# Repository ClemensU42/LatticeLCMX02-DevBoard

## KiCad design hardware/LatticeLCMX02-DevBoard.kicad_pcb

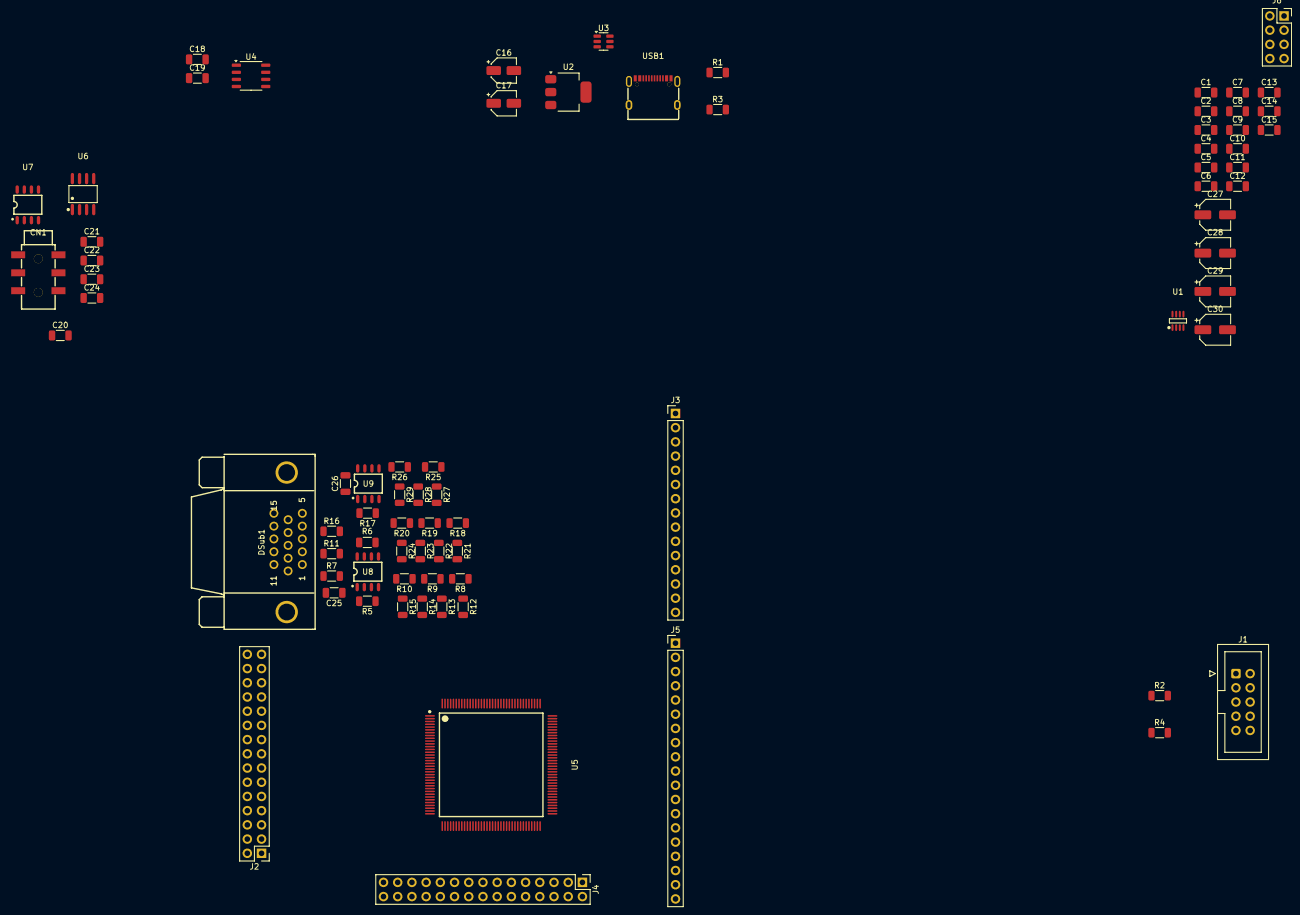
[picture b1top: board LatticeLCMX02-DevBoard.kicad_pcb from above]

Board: 4 copper layers, 77 parts (0 on the bottom side), 143 nets, no tracks yet.

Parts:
C1, C2, C3, C4, C5, C6, C7, C8, C9, C10, C11, C12, C13, C14, C15, C24, C25, C26: 470nF; C_1206_3216Metric
C16: 10µF; CP_Elec_4x5.4
C17: 22µF; CP_Elec_4x5.4
C18, C19: 0.1µF; C_1206_3216Metric
C20: 47µF; C_1206_3216Metric
C21, C22, C23: 100nF; C_1206_3216Metric
C27, C28, C29, C30: 47µF; CP_Elec_5x5.4
CN1: PJ-313D_C668608; AUDIO-SMD_PJ-313D-2
DSub1: DS1038-15FBNSIA74-0CC; DSUB-TH_DS1038-15FBNSIA74-0CC
J1: Conn_02x05_Odd_Even; IDC-Header_2x05_P2.54mm_Vertical
J2, J4: Conn_02x15_Counter_Clockwise; PinHeader_2x15_P2.54mm_Vertical
J3: Conn_01x15; PinHeader_1x15_P2.54mm_Vertical
J5: Conn_01x19; PinHeader_1x19_P2.54mm_Vertical
J6: Conn_02x04_Counter_Clockwise; PinSocket_2x04_P2.54mm_Vertical
R1, R3: 5k1; R_1206_3216Metric
R2, R4: 4k7; R_1206_3216Metric
R5, R6, R17: 220; R_1206_3216Metric
R7, R11, R16: 75; R_1206_3216Metric
R8, R9, R10, R18, R19, R20, R25, R26: 1k; R_1206_3216Metric
R12, R13, R14, R15, R21, R22, R23, R24, R27, R28, R29: 2k; R_1206_3216Metric
U1: RS0102YH8; SOT-23-8_L3.0-W1.7-P0.65-LS2.8-BL
U2: AMS1117-3.3; SOT-223-3_TabPin2
U3: USBLC6-2SC6; SOT-23-6
U4: CH340N; SOP-8_3.9x4.9mm_P1.27mm
U5: LCMXO2-4000HC-4TG144C; TQFP-144_L20.0-W20.0-P0.50-LS22.0-BL
U6: TM8211-TA2302; SOIC-8_L4.9-W3.9-P1.27-LS6.0-BL
U7, U8, U9: HG5532M/TR; SOP-8_L5.0-W3.9-P1.27-LS6.0-BL
USB1: TYPE-C 16PIN 2MD(073); USB-C-SMD_TYPE-C-6PIN-2MD-073

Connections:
+3.3V: C1.1, C2.1, C3.1, C4.1, C5.1, C6.1, C7.1, C8.1, C9.1, C10.1, C11.1, C12.1, C13.1, C14.1, C15.1, C17.1, C20.1, C21.1, C24.1, C25.1, C26.1, C27.1, C28.1, C29.1, C30.1, J1.6, J6.5, J6.6, J6.7, J6.8, R2.1, U1.1 (VCCB), U2.2 (VO), U5.7 (VCCIO5), U5.16 (VCCIO4), U5.30 (VCCIO3), U5.36 (VCC), U5.37 (VCCIO2), U5.51 (VCCIO2), U5.66 (VCCIO2), U5.72 (VCC), U5.79 (VCCIO1), U5.88 (VCCIO1), U5.102 (VCCIO1), U5.108 (VCC), U5.118 (VCCIO0), U5.123 (VCCIO0), U5.135 (VCCIO0), U5.144 (VCC), U6.5 (VDD), U7.8 (VCC), U8.8 (VCC), U9.8 (VCC)
+5V: C16.1, C18.1, U1.4 (OE), U1.8 (VCCA), U2.3 (VI), U3.5 (VBUS), U4.5 (VCC), USB1.2 (VBUS), USB1.11 (VBUS)
Audio_BCK: U5.139 (PT11A), U6.1 (BCK)
Audio_DIN: U5.141 (PT10A), U6.3 (DIN)
Audio_WS: U5.140 (PT10B), U6.2 (WS)
D+: U3.3 (I/O2), U3.4 (I/O2), U4.1 (UD+), USB1.6 (DP1), USB1.8 (DP2)
D-: U3.1 (I/O1), U3.6 (I/O1), U4.2 (UD-), USB1.5 (DN2), USB1.7 (DN1)
GND: C1.2, C2.2, C3.2, C4.2, C5.2, C6.2, C7.2, C8.2, C9.2, C10.2, C11.2, C12.2, C13.2, C14.2, C15.2, C16.2, C17.2, C18.2, C19.2, C20.2, C21.2, C22.2, C23.2, C24.2, C25.2, C26.2, C27.2, C28.2, C29.2, C30.2, CN1.1, DSub1.5, DSub1.6, DSub1.7, DSub1.8, DSub1.10, DSub1.16, DSub1.17, J1.2, J1.4, J1.8, J6.1, J6.2, J6.3, J6.4, R1.1, R3.1, R4.2, R12.2, R21.2, R27.2, U1.5 (GND), U2.1 (GND), U3.2 (GND), U4.3 (GND), U5.8 (GND), U5.18 (GND), U5.29 (GND), U5.46 (GND), U5.53 (GND), U5.64 (GND), U5.80 (GND), U5.90 (GND), U5.101 (GND), U5.116 (GND), U5.124 (GND), U5.134 (GND), U6.4 (GND), U7.4 (VEE), U8.3 (IN1+), U8.4 (VEE), U8.5 (IN2+), U9.3 (IN1+), U9.4 (VEE), U9.5 (IN2+), U9.6 (IN2-), USB1.1 (GND), USB1.12 (GND)
unnamed: DSub1.1, R7.1
unnamed: DSub1.2, R11.1
unnamed: DSub1.3, R16.1
unnamed: J2.1, U5.35 (PL20B)
unnamed: J2.2, U5.34 (PL20A)
unnamed: J2.3, U5.33 (PL19B)
unnamed: J2.4, U5.32 (PL19A)
unnamed: J2.5, U5.31 (PL18D)
unnamed: J2.6, U5.28 (PL17B)
unnamed: J2.7, U5.27 (PL17A)
unnamed: J2.8, U5.26 (PL16B)
unnamed: J2.9, U5.25 (PL16A)
unnamed: J2.10, U5.24 (PL14B)
unnamed: J2.11, U5.23 (PL14A)
unnamed: J2.12, U5.22 (PL13B)
unnamed: J2.13, U5.21 (PL13A)
unnamed: J2.14, U5.20 (PL10D)
unnamed: J2.15, U5.19 (PL10C)
unnamed: J2.16, U5.17 (PL10B)
unnamed: J2.17, U5.15 (PL10A)
unnamed: J2.18, U5.14 (PL9B)
unnamed: J2.19, U5.13 (PL9A)
unnamed: J2.20, U5.12 (PL8B)
unnamed: J2.21, U5.11 (PL8A)
unnamed: J2.22, U5.10 (PL7B)
unnamed: J2.23, U5.9 (PL7A)
unnamed: J2.24, U5.6 (PL6B)
unnamed: J2.25, U5.5 (PL6A)
unnamed: J2.26, U5.4 (PL4B)
unnamed: J2.27, U5.3 (PL4A)
unnamed: J2.28, U5.2 (PL3B)
unnamed: J2.29, U5.1 (PL3A)
unnamed: J3.1, U5.138 (PT11B)
unnamed: J3.2, U5.133 (PT14A)
unnamed: J3.3, U5.132 (PT14B)
unnamed: J3.4, U5.128 (PT18A)
unnamed: J3.5, U5.127 (PT18B)
unnamed: J3.6, U5.122 (PT21A)
unnamed: J3.7, U5.121 (PT21B)
unnamed: J3.8, U5.117 (PT24A)
unnamed: J3.9, U5.115 (PT24B)
unnamed: J3.10, U5.114 (PT25A)
unnamed: J3.11, U5.113 (PT25B)
unnamed: J3.12, U5.112 (PT27A)
unnamed: J3.13, U5.111 (PT27B)
unnamed: J3.14, U5.110 (PT28C)
unnamed: J3.15, U5.109 (PT28D)
unnamed: J4.1, U5.71 (PB30B)
unnamed: J4.2, U5.70 (PB30A)
unnamed: J4.3, U5.69 (PB29B)
unnamed: J4.4, U5.68 (PB29A)
unnamed: J4.5, U5.67 (PB27B)
unnamed: J4.6, U5.65 (PB27A)
unnamed: J4.7, U5.63 (PB24D)
unnamed: J4.8, U5.62 (PB24B)
unnamed: J4.9, U5.61 (PB24A)
unnamed: J4.10, U5.60 (PB23B)
unnamed: J4.11, U5.59 (PB23A)
unnamed: J4.12, U5.58 (PB21B)
unnamed: J4.13, U5.57 (PB21A)
unnamed: J4.14, U5.56 (PB20B)
unnamed: J4.15, U5.55 (PB20A)
unnamed: J4.16, U5.54 (PB15B)
unnamed: J4.17, U5.52 (PB15A)
unnamed: J4.18, U5.50 (PB13B)
unnamed: J4.19, U5.49 (PB13A)
unnamed: J4.20, U5.48 (PB10B)
unnamed: J4.21, U5.47 (PB10A)
unnamed: J4.22, U5.45 (PB9B)
unnamed: J4.23, U5.44 (PB9A)
unnamed: J4.24, U5.43 (PB7B)
unnamed: J4.25, U5.42 (PB7A)
unnamed: J4.26, U5.41 (PB4B)
unnamed: J4.27, U5.40 (PB4A)
unnamed: J4.28, U5.39 (PB3B)
unnamed: J4.29, U5.38 (PB3A)
unnamed: J5.1, U5.107 (PR2A)
unnamed: J5.2, U5.106 (PR2B)
unnamed: J5.3, U5.105 (PR3A)
unnamed: J5.4, U5.104 (PR3B)
unnamed: J5.5, U5.103 (PR4C)
unnamed: J5.6, U5.89 (PR10C)
unnamed: J5.7, U5.87 (PR10D)
unnamed: J5.8, U5.86 (PR13A)
unnamed: J5.9, U5.85 (PR13B)
unnamed: J5.10, U5.84 (PR14A)
unnamed: J5.11, U5.83 (PR14B)
unnamed: J5.12, U5.82 (PR15A)
unnamed: J5.13, U5.81 (PR15B)
unnamed: J5.14, U5.78 (PR16A)
unnamed: J5.15, U5.77 (PR16B)
unnamed: J5.16, U5.76 (PR18A)
unnamed: J5.17, U5.75 (PR18B)
unnamed: J5.18, U5.74 (PR19A)
unnamed: J5.19, U5.73 (PR19B)
unnamed: R9.2, R10.1, R15.1
unnamed: R8.1, R12.1, R13.1
unnamed: R8.2, R9.1, R14.1
unnamed: R18.1, R21.1, R22.1
unnamed: R18.2, R19.1, R23.1
unnamed: R19.2, R20.1, R24.1
unnamed: R25.1, R27.1, R28.1
unnamed: R25.2, R26.1, R29.1
unnamed: U1.2 (B1), U5.143 (PT9A)
unnamed: U1.3 (B2), U5.142 (PT9B)
unnamed: C19.1, U4.8 (V3)
unnamed: U6.6 (LCH), U7.3 (IN1+)
unnamed: U6.8 (RCH), U7.5 (IN2+)
unnamed: C22.1, CN1.3, U7.1 (OUT1), U7.2 (IN1-)
unnamed: C23.1, CN1.2, U7.6 (IN2-), U7.7 (OUT2)
unnamed: R5.1, R10.2, U8.2 (IN1-)
unnamed: R6.1, R20.2, U8.6 (IN2-)
unnamed: R5.2, R7.2, U8.1 (OUT1)
unnamed: R6.2, R11.2, U8.7 (OUT2)
unnamed: R17.1, R26.2, U9.2 (IN1-)
unnamed: R16.2, R17.2, U9.1 (OUT1)
unnamed: R1.2, USB1.4 (CC1)
unnamed: R3.2, USB1.10 (CC2)
PROG: J1.10, U5.119 (PT23D)
Serial_DX: U1.7 (A1), U4.6 (TXD)
Serial_RX: U1.6 (A2), U4.7 (RXD)
TCK: J1.1, R4.1, U5.131 (PT15C)
TDI: J1.5, U5.136 (PT13D)
TDO: J1.7, U5.137 (PT13C)
TMS: J1.3, R2.2, U5.130 (PT15D)
VGA_B_A: R28.2, U5.93 (PR9B)
VGA_B_B: R29.2, U5.94 (PR9A)
VGA_G_A: R22.2, U5.95 (PR8B)
VGA_G_B: R23.2, U5.96 (PR8A)
VGA_G_C: R24.2, U5.97 (PR6B)
VGA_HSYNC: DSub1.13, U5.91 (PR10B)
VGA_R_A: R13.2, U5.98 (PR6A)
VGA_R_B: R14.2, U5.99 (PR5B)
VGA_R_C: R15.2, U5.100 (PR5A)
VGA_VSYNC: DSub1.14, U5.92 (PR10A)

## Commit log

2025-04-13 Created Project
2025-04-21 Finished schematic
